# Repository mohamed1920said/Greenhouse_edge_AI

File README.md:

# Edge-AI Smart Greenhouse

This repository is an experimental greenhouse monitoring and control project built around an ESP32-class controller. It combines environmental sensors, relay-driven actuators, MQTT/Node-RED connectivity, over-the-air updates, persistent setpoints, and an Edge Impulse anomaly model. It also contains the project's firmware history and KiCad hardware designs.

The project is a prototype, not a finished safety controller. The firmware and PCB directories contain several generations with different assumptions. Start with `code section/final/final.ino` for the most integrated implementation, then verify it against the exact PCB and board you intend to use before compiling or wiring anything.

## System overview

```text
DHT22 + BH1750 + soil + flow + AC-voltage + DS1302
                         |
                         v
                    ESP32 tasks
              sensors / control / AI / MQTT
                 |                     |
                 v                     v
      heater, fan, pump,          MQTT broker
      humidifier, light           and Node-RED
```

The current `final.ino` uses FreeRTOS tasks to:

- sample temperature, humidity, light, soil moisture, water flow, AC voltage, and RTC time every two seconds;
- operate heater, fan, irrigation pump, humidifier, and grow light in automatic or manual mode;
- run an Edge Impulse anomaly classifier every five seconds and add rule-based fault diagnoses;
- publish state as JSON and accept JSON commands through MQTT every two seconds; and
- service Arduino OTA updates from the main loop.

Setpoints are stored in ESP32 Preferences/NVS and survive a restart.

## Repository map

| Path | Contents |
| --- | --- |
| `code section/final/final.ino` | Integrated firmware and the recommended starting point for review. |
| `code section/V0` through `V6`, and `V8` through `V11` | Historical firmware iterations. `V7` is not present; these are alternatives, not modules to compile together. |
| `code section/TEST PCB/CODE/CODE.ino` | PCB-oriented test firmware. |
| `code section/logger/` | Python serial logger and an example CSV log. |
| `code section/LIBRARY/GreenhouseDashboard .zip` | Archived dashboard-related project files. |
| `ia library/ei-mohamed_said-project-1-arduino-1.0.11.zip` | Exported Edge Impulse Arduino inference library used by `final.ino`. |
| `LIBRARY/` | Archived SimpleTimer and DHT library packages used during earlier iterations. |
| `NODE RED/flows.json` | Node-RED flow export. Review broker and topic settings before importing. |
| `PCB/central/` | KiCad central-board design and backups. |
| `PCB/central/external/` | KiCad external-board design, a nested `pfe` design, and backups. |
| `iot-dashboard`, `PCB/central/.history`, `PCB/central/external/.history` | Gitlink entries whose referenced repositories are not configured in this repository. |

Do not assume that a pin map or sensor type from an older `V*` directory matches `final.ino`; variants in this repository use different hardware and dependencies.

The three Gitlink entries above are stored like submodules, but there is no `.gitmodules` file with their source URLs. A normal clone therefore cannot retrieve their contents with `git submodule update`; the original repository locations would need to be identified and configured first.

## Current firmware pin map

The following table describes only `code section/final/final.ino`:

| Function | GPIO | Notes |
| --- | ---: | --- |
| BH1750 SDA / SCL | 8 / 9 | I2C address `0x23`. |
| DHT22 data | 4 | `DHTTYPE` is `DHT22`. |
| Soil-moisture analog input | 14 | Mapped from raw dry `3200` and wet `1100` to 0-100%; recalibrate for the actual probe. |
| Water-flow pulse input | 10 | Interrupt input with pull-up; conversion assumes 7.5 pulses per flow-rate unit. |
| Heater relay | 5 | Active low in the helper functions. |
| Fan relay | 6 | Active low. |
| Irrigation-pump relay | 7 | Active low. |
| Humidifier output | 15 | Active high, unlike the other actuator relays. |
| Light relay | 16 | Active low. |
| Red alarm LED | 42 | Driven high during configured lockout conditions. |
| AC-voltage analog input | 3 | Uses a firmware calibration factor of `237.0`; requires a safe isolated sensing circuit. |
| DS1302 CLK / DAT / RST | 11 / 12 / 13 | Three-wire RTC connection. |

These GPIO numbers are board-specific. Select an ESP32 variant that exposes them, check boot/strapping and ADC restrictions, and compare this table with the selected KiCad revision before connecting hardware.

## Firmware dependencies

Use an Arduino-compatible ESP32 development environment and install the libraries required by `final.ino`:

- DHT sensor library;
- BH1750;
- PubSubClient;
- ArduinoJson;
- a DS1302-compatible RTC library providing `ThreeWire.h` and `RtcDS1302.h`;
- the Edge Impulse Arduino library from `ia library/ei-mohamed_said-project-1-arduino-1.0.11.zip`; and
- the Wi-Fi, Preferences, ArduinoOTA, Wire, and FreeRTOS support supplied by the chosen ESP32 Arduino core.

Library and ESP32-core versions are not pinned. Record known-good versions after the first successful build.

## Configuration and first run

1. Review the schematic and choose the firmware/PCB revision that matches the assembled hardware.
2. Install the dependencies and import the Edge Impulse ZIP as an Arduino library.
3. In `final.ino`, replace `WIFI_SSID`, `WIFI_PASS`, `MQTT_SERVER`, and `MQTT_PORT` with values for the deployment network. Do not publish real credentials in source control.
4. Verify every GPIO, relay active level, soil calibration point, flow-sensor factor, and voltage-sensor calibration with actuators disconnected.
5. Start an MQTT broker reachable from the controller. The checked-in defaults point to `192.168.4.1:1883` without authentication or TLS.
6. Optionally import `NODE RED/flows.json`, then inspect all nodes and broker settings before deploying the flow. The exported flow targets HiveMQ Cloud over TLS on port 8883, while `final.ino` targets `192.168.4.1:1883` without TLS or authentication; the two configurations will not interoperate unchanged.
7. Build and upload `code section/final/final.ino`, open a serial monitor at `115200`, and validate sensor readings.
8. Test one low-voltage actuator channel at a time. Only connect pumps, heaters, or mains-powered equipment after the logic and fail-safe states have been independently verified.

`connectWiFi()` blocks until the configured network becomes available. A wrong SSID/password therefore prevents the remaining setup from completing.

## MQTT interface

The device uses these topics:

| Direction | Topic | Purpose |
| --- | --- | --- |
| Device to broker | `greenhouse/data` | Sensor values, actuator state, anomaly result, mode, setpoints, and manual commands. |
| Broker to device | `greenhouse/commands` | Mode, setpoint, and actuator-command changes. |

Example automatic-mode configuration:

```json
{
  "mode": "AUTO",
  "temp_low": 18,
  "temp_high": 26,
  "hum_low": 50,
  "lux_low": 50,
  "moist_low": 30
}
```

Example manual command:

```json
{
  "mode": "MANUAL",
  "heater": false,
  "fan": true,
  "pump": false,
  "humid": false,
  "light": true
}
```

Telemetry includes `temp`, `humid`, `lux`, `moist`, `water_flow`, `mains_voltage`, the five `*_state` fields, `anomaly_score`, `diagnosis`, `mode`, `hour`, the current setpoints, and the five `cmd_*` fields. Invalid DHT readings are published as JSON `null`.

## Automatic control and diagnostics

The checked-in defaults are 18-26 deg C, 50% minimum humidity, 50 lux minimum light, and 30% minimum soil moisture. In automatic mode:

- the heater runs below the low-temperature setpoint and the fan above the high-temperature setpoint;
- the humidifier runs below the humidity setpoint;
- the pump runs below the soil-moisture setpoint; and
- the light uses a 150-lux off hysteresis above its on threshold.

The AI input repeats temperature, humidity, soil moisture, light, and water-flow values across the model frame. Rule-based diagnoses take priority for invalid DHT data, pump-without-flow, flow-without-pump, low temperature while heating, and low humidity while humidifying. An anomaly score above `3.0` otherwise produces a warning.

The controller switches off selected loads and lights the red LED when measured AC voltage is between 10 V and 190 V, or when the diagnosis contains `CRITICAL`. This logic is an application safeguard, not certified electrical protection.

## Known limitations

- Wi-Fi credentials and broker details are hard-coded. MQTT has no authentication or TLS, and OTA has no configured password.
- The code reads the RTC hour but currently sets `isDaytime = true`; automatic lighting is therefore not actually limited to the stated day period.
- The AC-voltage calculation assumes a particular 240 V sensor calibration. It must not be connected directly to mains, and its values are not reliable on different hardware without calibration.
- Brownout lockout is applied only when the measured voltage is above 10 V and below 190 V. A disconnected or failed sensing circuit that reports 0 V bypasses this check rather than forcing a safe state.
- On a DHT failure, automatic temperature/humidity branches skip new commands, so prior fan or humidifier states can remain latched. The resulting `CRITICAL` path explicitly switches off only the heater and pump; it does not force every actuator off.
- Soil and flow conversions use fixed calibration constants. Edge Impulse results are meaningful only if sensor order, units, preprocessing, and library export match the model's training data.
- Relay polarity is mixed: the humidifier is active high while the other actuator helpers are active low.
- Historical firmware, archived libraries, Node-RED flow, and PCB backups can conflict with the final sketch. There is no single checked-in bill of materials or version manifest tying them together.
- Three Gitlink entries have no matching `.gitmodules` configuration, so the dashboard and history content they reference is not reproducible from this repository alone.
- Control and network loops have not been demonstrated here as fault tolerant. Network loss, MCU reset, stuck relays, sensor disconnection, dry running, and watchdog behavior require explicit tests.

## Safety

Heaters, pumps, humidifiers, grow lights, relays, water, and mains sensing create fire, shock, flooding, and equipment hazards. Use isolated and correctly rated power supplies, relay/driver modules, fuses, grounding, enclosures, strain relief, emergency shutoff, and independent temperature/water-level protection. Keep low-voltage electronics separated from mains and wet areas. Test with safe dummy loads first, and do not operate this prototype unattended or use it as the only protection for plants, property, or people.

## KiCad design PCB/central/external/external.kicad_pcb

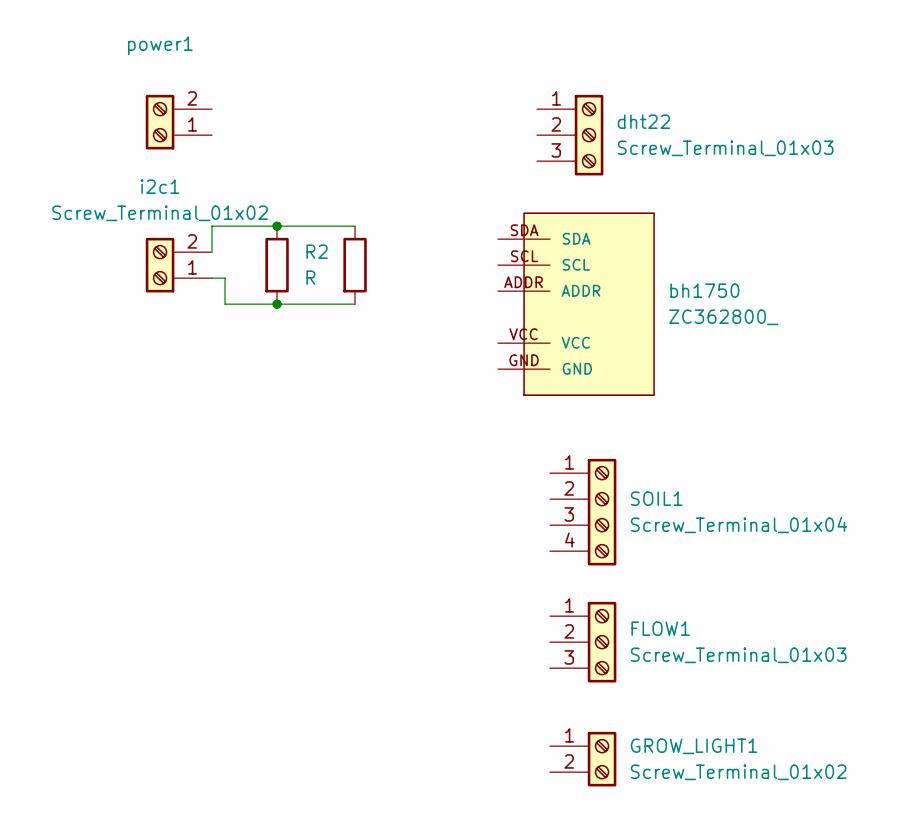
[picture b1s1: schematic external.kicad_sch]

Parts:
FLOW1: Screw_Terminal_01x03; water flow
GROW_LIGHT1: Screw_Terminal_01x02; TerminalBlock_bornier-2_P5.08mm
R1, R2: R; R_Axial_DIN0204_L3.6mm_D1.6mm_P5.08mm_Horizontal
SOIL1: Screw_Terminal_01x04; soil moist
bh1750: ZC362800_; bh1750
dht22: Screw_Terminal_01x03; dht22
i2c1: Screw_Terminal_01x02; TerminalBlock_bornier-2_P5.08mm
power1: Screw_Terminal_01x02; TerminalBlock_bornier-2_P5.08mm

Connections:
unnamed: R1.2, R2.2, i2c1.1
unnamed: R1.1, R2.1, i2c1.2

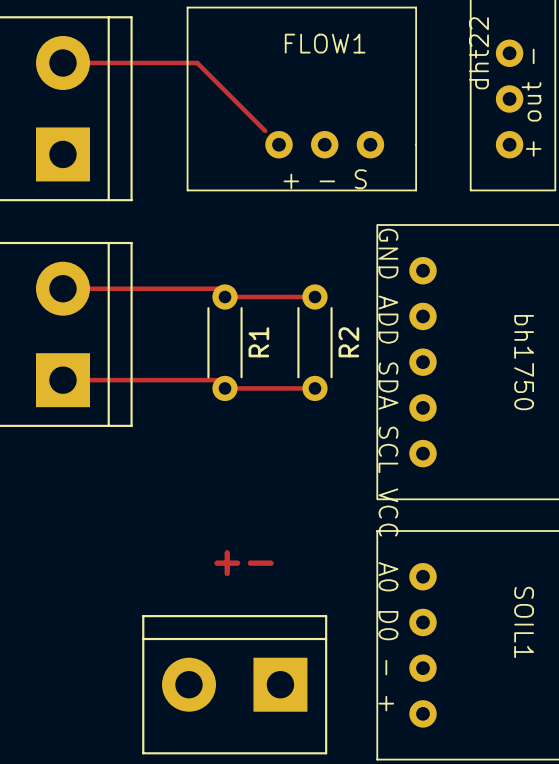
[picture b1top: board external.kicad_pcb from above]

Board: 2 copper layers, 9 parts (0 on the bottom side), 2 nets.

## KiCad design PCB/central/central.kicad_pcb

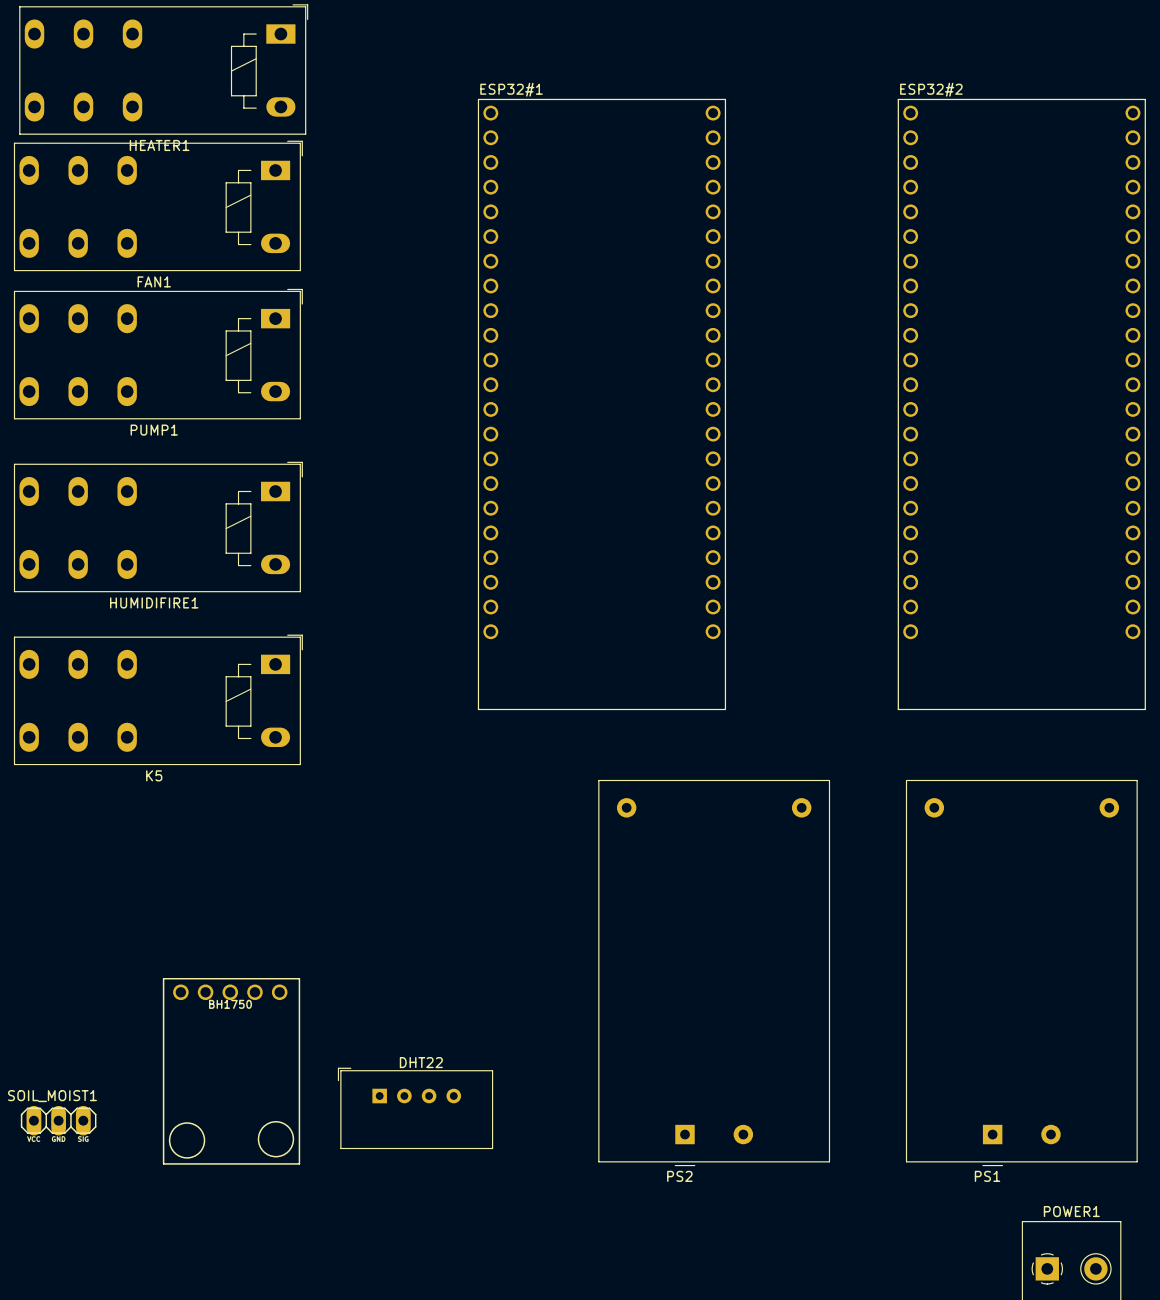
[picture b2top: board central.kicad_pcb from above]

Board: 2 copper layers, 13 parts (0 on the bottom side), 14 nets, no tracks yet.

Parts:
BH1750: ZC362800_
DHT22: AM2302; ASAIR_AM2302_P2.54mm_Vertical
ESP32#1, ESP32#2: ESP32-S3-DEVKITC-1U-N8R8; MODULE_ESP32-S3-DEVKITC-1U-N8R8
FAN1: RT314A05; Relay_SPDT_Schrack-RT1-16A-FormC_RM5mm
HEATER1: RT314A05; Relay_SPDT_Schrack-RT1-16A-FormC_RM5mm
HUMIDIFIRE1: RT314A05; Relay_SPDT_Schrack-RT1-16A-FormC_RM5mm
K5: GROW_LIGHT; Relay_SPDT_Schrack-RT1-16A-FormC_RM5mm
POWER1: Screw_Terminal_01x02; TerminalBlock_Philmore_TB132_1x02_P5.00mm_Horizontal
PS1: HLK-5M05; Converter_ACDC_HiLink_HLK-5Mxx
PS2: HLK-5M12; Converter_ACDC_HiLink_HLK-5Mxx
PUMP1: RT314A05; Relay_SPDT_Schrack-RT1-16A-FormC_RM5mm
SOIL_MOIST1: SEN-13322

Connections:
3V3: ESP32#1.J1_1 (3V3), ESP32#1.J1_2 (3V3), ESP32#2.J1_1 (3V3), ESP32#2.J1_2 (3V3)
5V: BH1750.VCC, DHT22.1 (VDD), ESP32#2.J1_21 (5V0), HUMIDIFIRE1.11, K5.11, PS1.4 (+Vout), SOIL_MOIST1.1 (VCC)
12V: FAN1.11, HEATER1.11, PS2.4 (+Vout), PUMP1.11
GND: BH1750.GND, DHT22.3 (GND), DHT22.4 (GND), ESP32#1.J1_22 (GND), ESP32#1.J3_1 (GND), ESP32#1.J3_21 (GND), ESP32#1.J3_22 (GND), ESP32#2.J1_22 (GND), ESP32#2.J3_1 (GND), ESP32#2.J3_21 (GND), ESP32#2.J3_22 (GND), FAN1.A1, HEATER1.A1, HUMIDIFIRE1.A1, K5.A1, PS1.3 (-Vout), PS2.3 (-Vout), PUMP1.A1, SOIL_MOIST1.2 (GND)
unnamed: POWER1.1, PS1.1 (AC/L), PS2.1 (AC/L)
unnamed: POWER1.2, PS1.2 (AC/N), PS2.2 (AC/N)
PIN_5: ESP32#1.J1_5 (GPIO5), HEATER1.A2
PIN_6: ESP32#1.J1_6 (GPIO6), FAN1.A2
PIN_7: ESP32#1.J1_7 (GPIO7), PUMP1.A2
PIN_8: BH1750.SDA, ESP32#1.J1_12 (GPIO8)
PIN_9: BH1750.SCL, ESP32#1.J1_15 (GPIO9)
PIN_14: ESP32#1.J1_20 (GPIO14), SOIL_MOIST1.3 (SIG)
PIN_15: ESP32#1.J1_8 (GPIO15), HUMIDIFIRE1.A2
PIN_16: ESP32#1.J1_9 (GPIO16), K5.A2
